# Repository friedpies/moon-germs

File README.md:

## Moon Germs
#### A hand-held, battery powered digital synthesizer based on the Teensy 3.2 and Audio Shield by www.pjrc.com

### Updates 10/21/18
*After making it into the semi-finals for the 2018 Hackaday challenge, I thought it would be fun to add some fun new features before submitting this project to the finals. In the past couple of days I've built a desktop app using Processing that connects to the device and allows you to update parameters in real time. I restructured the synth engine to include a LowPass filter and LFO. It was a pretty ambitious goal for me and I still have a lot of bugs to work out, but I have an MVP that works pretty well and looks pretty awesome too. See below for details about the app.*

### About the Device
A fun, pocket-sized synthesizer that uses an IR proximity sensor to modulate frequency. Using a combination of buttons and triggers, the device can produce several different waveforms and effects. An 8x8 LED matrix shows useful and colorful information while in use. Currently finishing up Rev 1.0

I wanted to explore digital synthesis using the Teensy Audio shield and experiment with a unique way of interacting with a synthesizer with minimal buttons/knobs, all while designing a device with an interesting and cyberpunk-y form factor. Although I'm a lifelong musician, I never really explored synthesis before and thought this would be a great way to dive in. This has been an awesome learning experience and has gotten me hooked! I'm excited to keep this up.

Traditional synthesizers can be intimidating to approach with all of their knobs, sliders and weird nomenclature, and difficult for a beginner to understand. This project aims to provide a fun and addicting way to mess around with a couple different waveforms and  explore creative and strange musical ideas. With only 4 buttons, and 2 analog inputs, interacting with the Moon Germs synthesizer and creating sound is really simple. Simply press down the "play" button and move your hand around relative to the IR sensor. Cycle through various waveforms with button 2, and switch octaves with buttons 3 & 4. For a "fatter" sound, apply force to the trigger to detune oscillator 2. The 8x8 display shows what type of waveform you're hearing, and dynamically speeds up or slows down with pitch.

When you're ready to take a deeper dive into the behind-the-scenes of synthesis, connect the device to the desktop app to adjust and tweak various parameters in a non-intimidating environment. Once connected, the app auto-loads the device's stored parameters according to their bank number. In addition to waveform selection, the adjustable parameters include oscillator volumes, detune amount, filter On/Off, cutoff, resonance, LFO on/off, rate, and amount. Additionally there is a trigger assignment option which allows the trigger to dynamic adjust parameters in real-time outside of the app. Currently, parameter adjustments will be saved on the device after disconnect, but will reset after a power cycle.

The entire design was made using open/free software and can be rebuilt with accessible tools and open electronics modules (see BOM).

--------
### Usage
The Moon Germs' synthesis engine is shown in the photo below. Pressing down button 1 activates the oscillators while their frequency is determined by the IR sensor. Button 2 cycles through 4 waveforms (saw, square, reverse saw, and triangle). Buttons 3 & 4 shift octaves up & down respectively. The spring loaded trigger applies a detune to oscillator 2. In standalone mode (not connected to the app), the filter and LFO are turned OFF for simplicity.

### Desktop App
 Connecting the device to the desktop app allows the user to adjust various parameters to explore sound design. Once connected, the app auto-loads the device's stored parameters according to their bank number. In addition to waveform selection, the adjustable parameters include oscillator volumes, detune amount, filter On/Off, cutoff, resonance, LFO on/off, rate, and amount. Additionally there is a trigger assignment option which allows the trigger to dynamic adjust parameters in real-time outside of the app. Currently, parameter adjustments will be saved on the device after disconnect, but will reset after a power cycle.

Desktop App Detail Information can be found [here](https://github.com/friedpies/moon-germs/tree/master/Desktop%20App)

--------
### Video Demos
[Submission Video](https://youtu.be/npFgwcqw3Ks)

[Demo 1](https://youtu.be/qyO1_fC_Kus)

[Demo 2](https://youtu.be/aUcpQy3lOxo)

--------
### BOM and Build Instructions
Full BOM and assembly instructions found [here](https://github.com/friedpies/moon-germs/blob/master/BUILD_INSTRUCTIONS.md)

--------
###  Electronics
- Schematic, Board, and CAM can be found [here](https://github.com/friedpies/moon-germs/tree/master/Eagle)
- PCB was manufactured using https://www.seeedstudio.com/fusion.html
--------
### Code
Arduino Code can be found [here](https://github.com/friedpies/moon-germs/tree/master/Arduino/moonGerms)

--------
### CAD + 3D Printing
STEP files of full assembly and STL files for 3D printing can be found [here](https://github.com/friedpies/moon-germs/tree/master/CAD)

--------
### Acknowledgments
- [PJRC](www.pjrc.com) for developing such a great audio shield and great tutorials, this thing is awesome!
- [Notes and Volts](www.notesandvolts.com) for such useful tutorials on how to use the Teensy Audio shield
- [LED Matrix Editor](https://xantorohara.github.io/led-matrix-editor/) A great GUI for creating 8x8 matrix animations.
- [Adafruit](www.adafruit.com) for their great electronics modules and Arduino libraries.
- Several [GrabCAD](www.grabcad.com) users for uploading and sharing their component models (shoutouts in /CAD folder)
- Shoutout to my cousin, Justin Marut, for translating "Moon Germs" into Japanese for me

--------
### Author & License
Author: Kenneth Marut (www.kennethmarut.com)

License: MIT

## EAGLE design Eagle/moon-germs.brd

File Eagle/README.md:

ECAD files were designed and generated using Autodesk Eagle and manufactured using [Seeed Studio Fusion](www.seeedstudio.com)

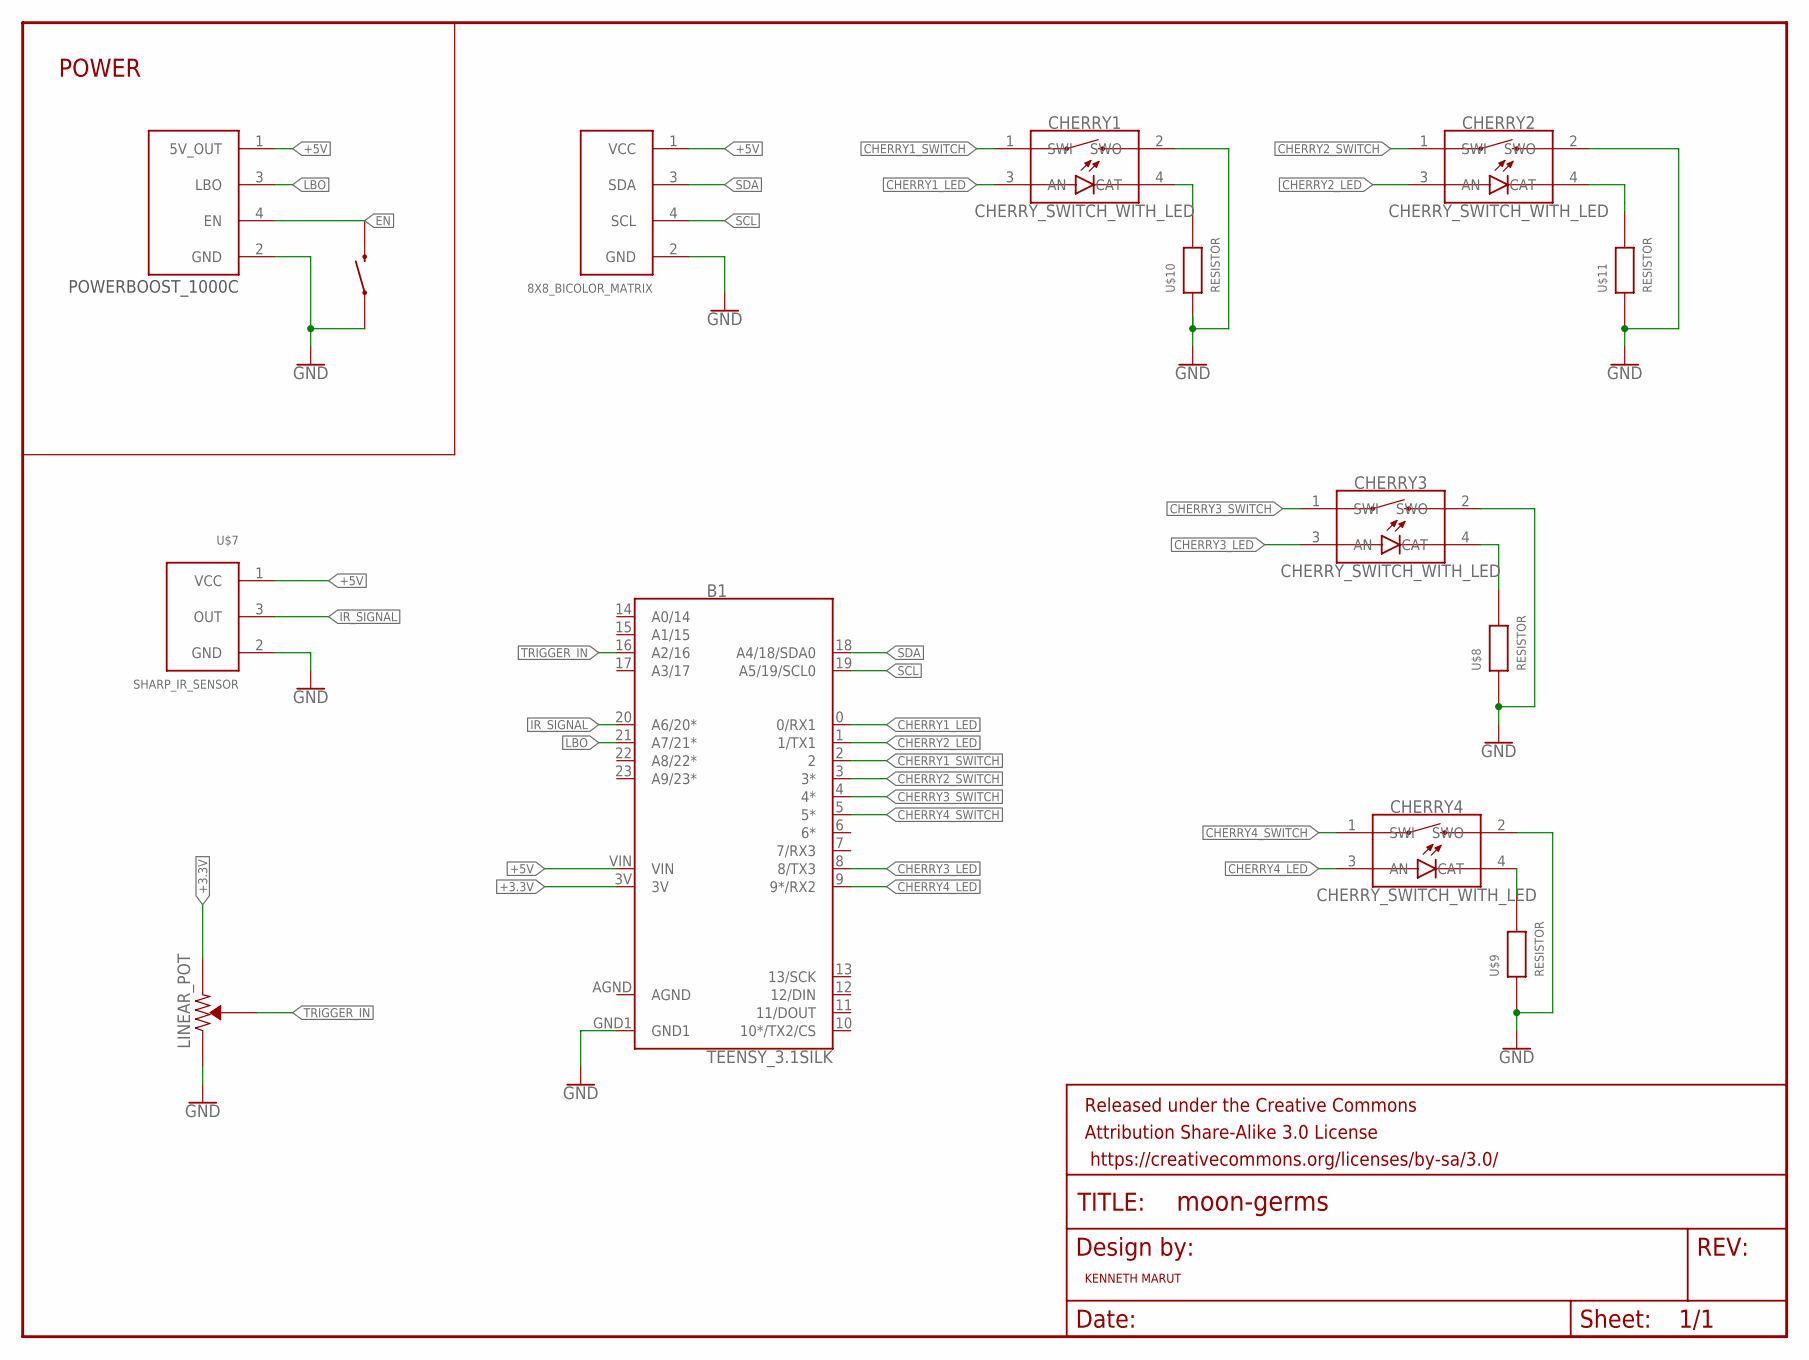
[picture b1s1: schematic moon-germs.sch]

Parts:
B1: TEENSY_3.1SILK; TEENSY_3.1
CHERRY1, CHERRY2, CHERRY3, CHERRY4: CHERRY_SWITCH_WITH_LED; 1X04
FRAME1: FRAME-LETTER; CREATIVE_COMMONS
U$1: 8X8_BICOLOR_MATRIX; 1X04
U$6: SPST-SWITCH; 1X02
U$7: SHARP_IR_SENSOR; 1X03
U$8, U$9, U$10, U$11: RESISTOR; 0805
U$12: POWERBOOST_1000C; 1X04
U$13: LINEAR_POT; 1X03

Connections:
+3.3V: B1.3V, U$13.1 (+)
+5V: B1.VIN, U$1.1 (VCC), U$7.1 (VCC), U$12.1 (5V_OUT)
AGND: B1.AGND
CHERRY1_LED: B1.0 (0/RX1), CHERRY1.3 (AN)
CHERRY1_SWITCH: B1.2, CHERRY1.1 (SWI)
CHERRY2_LED: B1.1 (1/TX1), CHERRY2.3 (AN)
CHERRY2_SWITCH: B1.3 (3*), CHERRY2.1 (SWI)
CHERRY3_LED: B1.8 (8/TX3), CHERRY3.3 (AN)
CHERRY3_SWITCH: B1.4 (4*), CHERRY3.1 (SWI)
CHERRY4_LED: B1.9 (9*/RX2), CHERRY4.3 (AN)
CHERRY4_SWITCH: B1.5 (5*), CHERRY4.1 (SWI)
EN: U$6.2 (SWO), U$12.4 (EN)
GND: B1.GND1, CHERRY1.2 (SWO), CHERRY2.2 (SWO), CHERRY3.2 (SWO), CHERRY4.2 (SWO), U$1.2 (GND), U$6.1 (SWI), U$7.2 (GND), U$8.1, U$9.1, U$10.1, U$11.1, U$12.2 (GND), U$13.3 (-)
IR_SIGNAL: B1.20 (A6/20*), U$7.3 (OUT)
LBO: B1.21 (A7/21*), U$12.3 (LBO)
unnamed: CHERRY1.4 (CAT), U$10.2
unnamed: CHERRY4.4 (CAT), U$9.2
unnamed: CHERRY3.4 (CAT), U$8.2
unnamed: CHERRY2.4 (CAT), U$11.2
SCL: B1.19 (A5/19/SCL0), U$1.4 (SCL)
SDA: B1.18 (A4/18/SDA0), U$1.3 (SDA)
TRIGGER_IN: B1.16 (A2/16), U$13.2 (W)

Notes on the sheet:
KENNETH MARUT
POWER

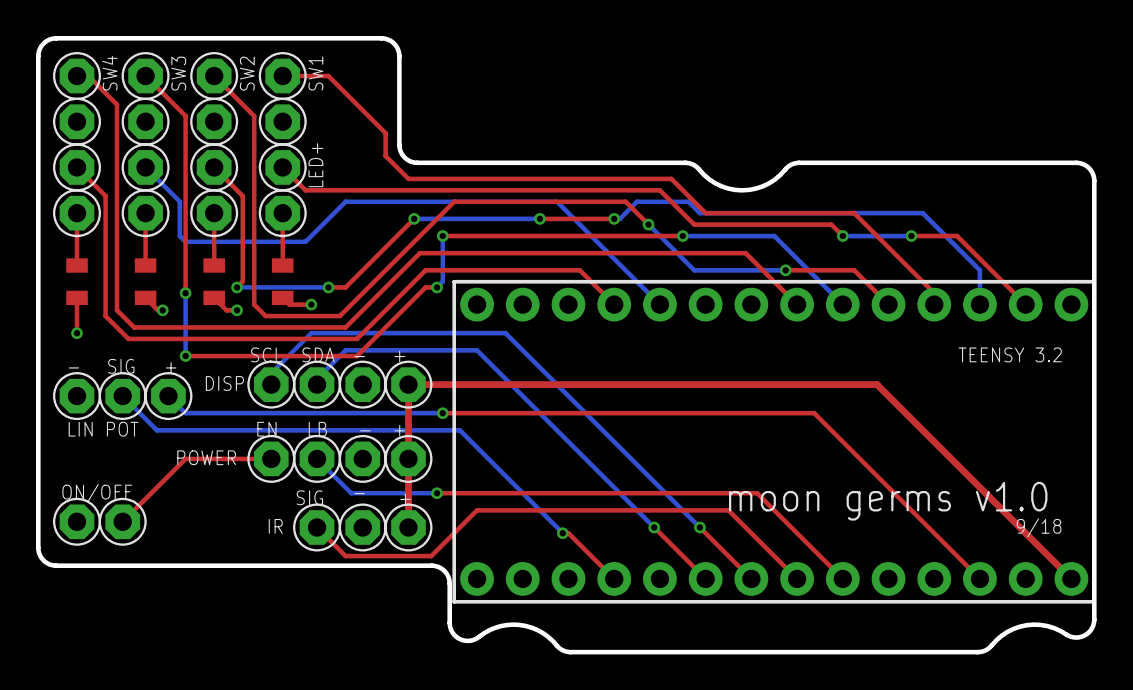
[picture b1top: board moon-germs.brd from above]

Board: 2 copper layers, 58.7 x 34.1 mm, 15 parts (0 on the bottom side), 21 nets.

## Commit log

2018-09-18 added some basic functionality
2018-09-18 messing around
2018-09-23 Getting synth to work
2018-09-25 Added button functionality
2018-09-25 Added animation frequency update
2018-09-30 Added more animations
2018-10-04 Fixed glitch in display
2018-10-05 Fixed glitch, added detune functionality
2018-10-05 Adding Readme and documentation
2018-10-05 minor readme updates
2018-10-05 Updating readme
2018-10-05 Added photos
2018-10-05 Create LICENSE
2018-10-05 added photo
2018-10-05 added additional assets
2018-10-05 added renderings
2018-10-05 added 3D print files
2018-10-05 added more renderings
2018-10-07 added more images
2018-10-07 changed frequency mapping, added gif of spring
2018-10-07 resized image
2018-10-08 Minor changes
2018-10-08 updating build instructions
2018-10-08 updating photos
2018-10-08 added image
2018-10-08 photos
2018-10-08 updated photo
2018-10-08 updated instructions, added trigger image
2018-10-08 finished build instructions
2018-10-08 fixed photo
2018-10-08 updated build instructions
2018-10-08 fixed readme
2018-10-17 Added state machine and desktop folder
2018-10-17 Added buttons and knobs etc. building out GUI
2018-10-18 data being passed from app successful
2018-10-19 working on splash screen
2018-10-19 updated assets
2018-10-19 added splash screen pixelation (For fun)
2018-10-19 updated audio block diagram, slowly adding variable updates
2018-10-19 More progress, simplified engine
2018-10-20 added more assets, variable update functions
2018-10-20 fixed bug in spacebar
2018-10-20 tired of coding, working on UI for app
2018-10-20 more app design stuff
2018-10-20 rethinking save/restore feature
2018-10-20 got trigger destinations working
2018-10-20 writing load function
2018-10-21 sending data and loading is successful
2018-10-21 repeatable loading bug
2018-10-21 redesigned interface, tired from coding
2018-10-21 simplifying, getting close!
2018-10-22 tons of updates, moved everything to use serial events, should've done that before...dummy
2018-10-22 working, still need to figure out save and refactor
2018-10-22 animation updates finally working
2018-10-22 working, still need save option
2018-10-22 cleaning up extra files
2018-10-22 Updating readme, adding assets etc.
2018-10-22 continuing to update readme
2018-10-22 more updates
2018-10-22 readme udpates
2018-10-22 Added app downloads
2018-10-22 added assets
2018-10-22 updated app readme
2018-10-22 fixed folder structure
2018-10-22 more readme updates
2018-10-22 added more assets
2018-10-22 fixed some readme errors
2018-10-22 Readme updates
2018-10-22 added submission video to readme
2018-10-22 mentioned gui library
2018-10-31 added an FFT (no functionality yet) and removed some redundant code

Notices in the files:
parts and their libraries:
SparkFun-Retired: Licensing: Creative Commons ShareAlike 4.0 International - https://creativecommons.org/licenses/by-sa/4.0
SparkFun-Retired: Released under the Creative Commons Attribution Share-Alike 3.0 License
SparkFun-Retired: https://creativecommons.org/licenses/by-sa/3.0
